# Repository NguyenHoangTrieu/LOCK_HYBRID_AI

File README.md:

# LOCK_HYBRID_AI

Face and RFID attendance / access-control system. A door-mounted **Edge AI Node**
detects faces and reads RFID cards; a **Cloud Backend** identifies people, stores
attendance records, and serves an admin web app. Full detail lives in
[ARCHITECTURE.md](ARCHITECTURE.md) (design) and [SYSTEM_REQUIREMENTS.md](SYSTEM_REQUIREMENTS.md)
(requirements, IEEE 830 / ISO-IEC-IEEE 29148 style). For "what actually
happened and what's still open" across the whole repo (not just one
subproject), see [WORKLOG.md](WORKLOG.md).

## Why the split

The door device can run a small model that finds faces, but not the much
larger model that identifies them, and it can't hold the user database. So
the device answers *"is someone there?"* and the server answers *"who is
it?"* (CON-7, CON-8 in the SRS).

```mermaid
graph LR
    EDGE["Edge AI Node<br/>detects faces, reads cards, opens the latch"]
    CLOUD["Cloud Backend<br/>identifies people, stores records, serves admin UI"]
    EDGE -->|"face image or card UID"| CLOUD
    CLOUD -->|"decision + unlock command"| EDGE
```

## Repository Layout

```
LOCK_HYBRID_AI/
  ARCHITECTURE.md          <- system design, sequence/state diagrams, build order
  SYSTEM_REQUIREMENTS.md   <- SRS: functional, performance, accuracy, safety requirements
  EDGE_NODE/                <- door-side firmware (FRDM-MCXN947 + camera + RFID + LCD + latch)
    Camera_AI_Test1/          <- camera capture + on-device NPU face-detection bring-up project
  PCB_DES/                  <- hardware / PCB design
    LOCK_EDGE_BASEBOARD/
  CLOUD_SERVER/              <- recognition service, database, admin web app (not yet started)
```

### EDGE_NODE

`EDGE_NODE/Camera_AI_Test1` is the bring-up project for the edge device's
camera + on-NPU face-**detection** pipeline (OV7670 → SmartDMA → Edge
Impulse FOMO model on the Neutron NPU → LCD status / SD snapshot), copied
in from the standalone `Camera_AI_Test1` prototype. It proves out CON-1,
CON-3, and CON-7 from the SRS: an FRDM-MCXN947 board driving an OV7670
camera and running face detection on the integrated NPU without the
general-purpose CPU doing the main computation.

This copy keeps its own `README.md` (build/flash instructions, pinout,
hardware notes) and `ARCHITECTURE.md` (design decisions, NPU integration
details), but drops `KNOWLEDGE.md` (a general concepts primer) and
`WORKLOG.md` (the standalone prototype's dated bring-up log) — those
documented the independent history of the prototype and don't apply once
folded into this repo. The firmware source, board port, and AI model files
are unchanged from the original project.

RFID (MFRC522), servo-latch control (fail-locked, HI-3/HI-4/SR-6), the
ARCHITECTURE.md §2.4 state machine, and now the ESP32-C5 network
transport (CON-2, CI-1 to CI-5 - both the ESP-IDF firmware in
`EDGE_NODE/firmware/esp32_net_bridge/` and the MCXN947-side SPI driver)
are implemented and build clean on both sides. None of this has been
flashed to real hardware yet, and the ESP32<->MCXN947 link in particular
has not been verified between two physical boards - see
`EDGE_NODE/firmware/esp32_net_bridge/README.md`. Still missing: offline
event buffering (FR-19 to FR-25) and a real recognition model on the
server (see `CLOUD_SERVER/README.md`).

### CLOUD_SERVER

FastAPI + SQLite implementation of ARCHITECTURE.md §3: device auth, the
face/card attendance API, attendance records with cooldown, and an admin
web app (enrollment, cards, reports, config) - see
[CLOUD_SERVER/README.md](CLOUD_SERVER/README.md). Verified end-to-end
against a running instance, including through the browser UI, not just
written against the spec. The one piece that is a placeholder rather than
real: the recognition model itself (no face-detection/embedding model is
wired in - see that README's Status section before trusting any accuracy
number). Not implemented: TLS termination (put a reverse proxy in front
for real deployment) and offline event buffering on the device side to
actually feed `/attendance/batch`.

### PCB_DES

Hardware/PCB design files for the edge baseboard (`LOCK_EDGE_BASEBOARD`).

## Build Order

See ARCHITECTURE.md §6 for the full sequencing rationale. In short: bring
up peripherals in isolation, stand up a stub server API, wire the network
path end to end, get card-based attendance fully working with no AI
involved, then bring in the detection model on the device and recognition
on the server.

## Known Limitations (by design, this release)

- **No presentation-attack (spoofing) detection** — a photo of an enrolled
  person may be sufficient to obtain access (SR-7). Sites needing
  protection against this must not rely on face recognition as the sole
  access control.
- Face-based access is not available while offline; only card-based access
  can optionally work offline, using cached authorization data (FR-23,
  FR-24).

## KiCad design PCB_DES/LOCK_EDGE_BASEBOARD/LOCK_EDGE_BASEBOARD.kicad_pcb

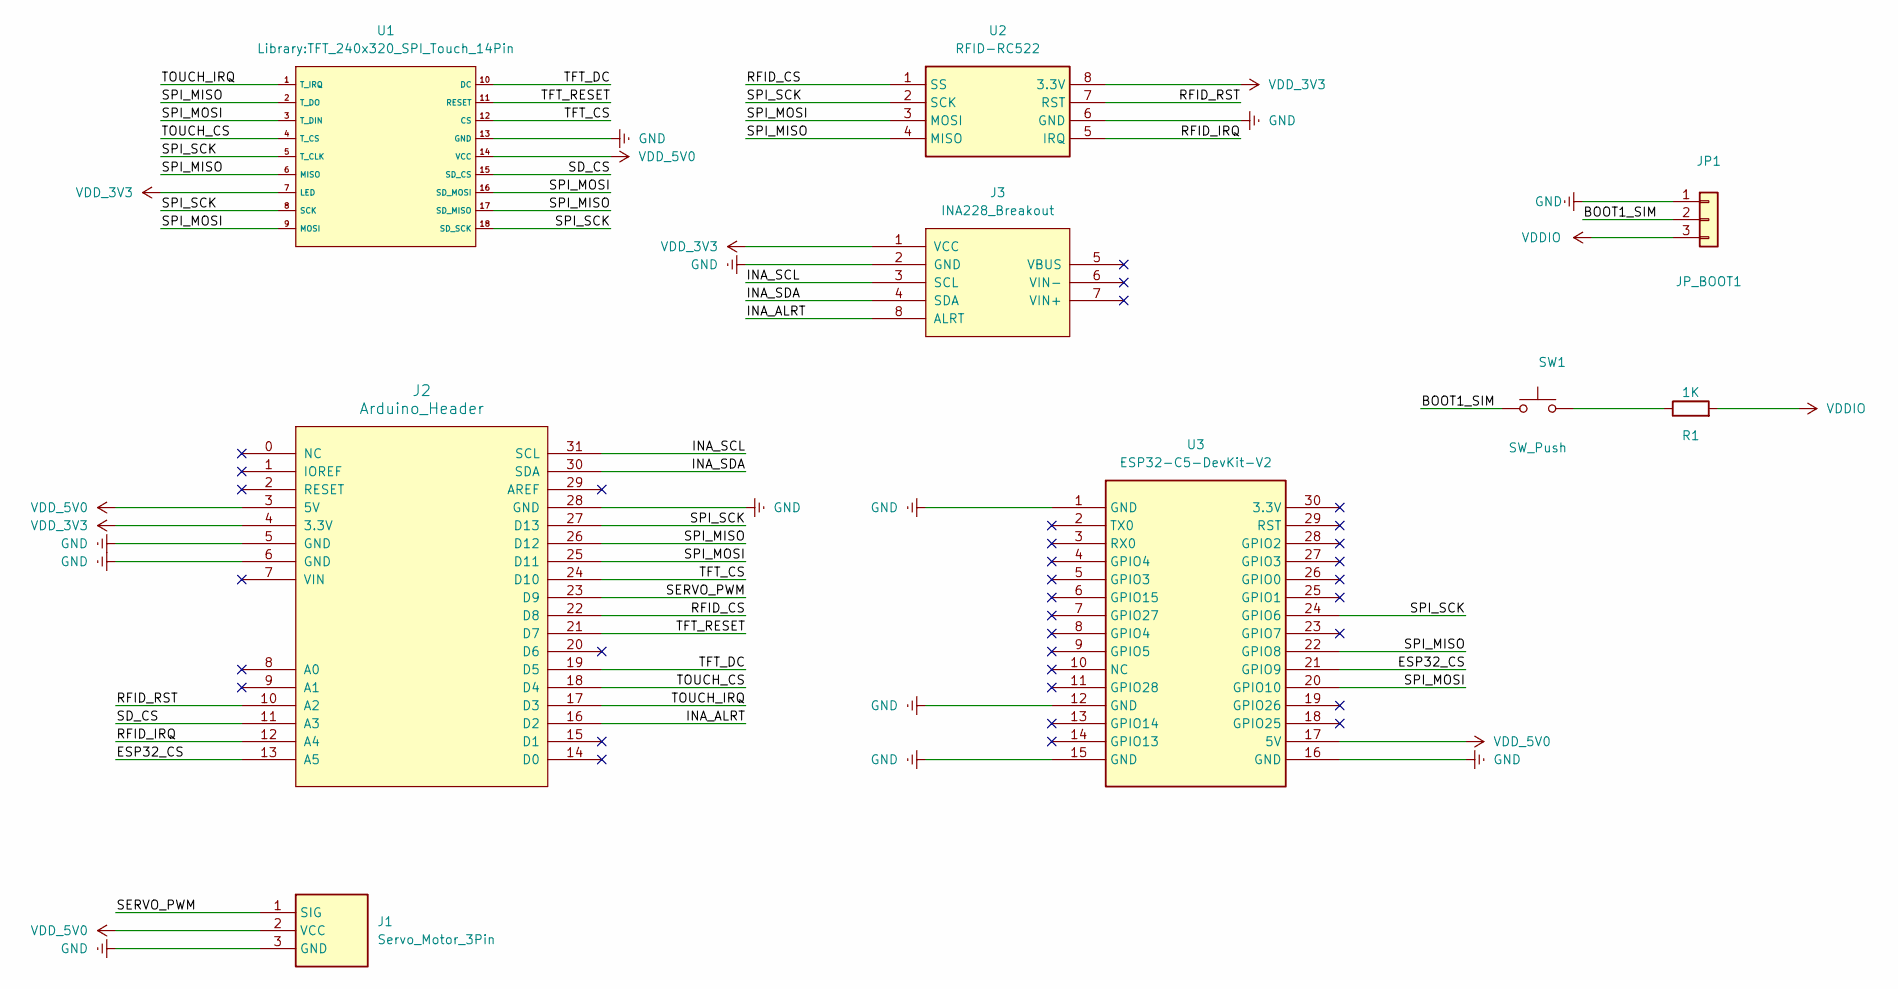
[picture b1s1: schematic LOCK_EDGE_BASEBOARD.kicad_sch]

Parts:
J1: Servo_Motor_3Pin; Servo_Header_1x03_P2.54mm
J2: Arduino_Header
J3: INA228_Breakout; INA228_Breakout_Socket
JP1: JP_BOOT1; JP_Header_1x03_P2.54mm
R1: 1K; R_1206_3216Metric_Pad1.30x1.75mm_HandSolder
SW1: SW_Push; SW_PUSH_6mm
U1: TFT_240x320_SPI_Touch_14Pin
U2: RFID-RC522; RFID-RC522_Header_1x08_P2.54mm
U3: ESP32-C5-DevKit-V2

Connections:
/BOOT1_SIM: JP1.2, SW1.1
/ESP32_CS: J2.13 (A5), U3.21 (GPIO9)
/INA_ALRT: J2.16 (D2), J3.8 (ALRT)
/INA_SCL: J2.31 (SCL), J3.3 (SCL)
/INA_SDA: J2.30 (SDA), J3.4 (SDA)
/RFID_CS: J2.22 (D8), U2.1 (SS)
/RFID_IRQ: J2.12 (A4), U2.5 (IRQ)
/RFID_RST: J2.10 (A2), U2.7 (RST)
/SD_CS: J2.11 (A3), U1.15 (SD_CS)
/SERVO_PWM: J1.1 (SIG), J2.23 (D9)
/SPI_MISO: J2.26 (D12), U1.2 (T_DO), U1.6 (MISO), U1.17 (SD_MISO), U2.4 (MISO), U3.22 (GPIO8)
/SPI_MOSI: J2.25 (D11), U1.3 (T_DIN), U1.9 (MOSI), U1.16 (SD_MOSI), U2.3 (MOSI), U3.20 (GPIO10)
/SPI_SCK: J2.27 (D13), U1.5 (T_CLK), U1.8 (SCK), U1.18 (SD_SCK), U2.2 (SCK), U3.24 (GPIO6)
/TFT_CS: J2.24 (D10), U1.12 (CS)
/TFT_DC: J2.19 (D5), U1.10 (DC)
/TFT_RESET: J2.21 (D7), U1.11 (RESET)
/TOUCH_CS: J2.18 (D4), U1.4 (T_CS)
/TOUCH_IRQ: J2.17 (D3), U1.1 (T_IRQ)
GND: J1.3 (GND), J2.5 (GND), J2.6 (GND), J2.28 (GND), J3.2 (GND), JP1.1, U1.13 (GND), U2.6 (GND), U3.1 (GND), U3.12 (GND), U3.15 (GND), U3.16 (GND)
unnamed: R1.1, SW1.2
VDDIO: JP1.3, R1.2
VDD_3V3: J2.4 (3.3V), J3.1 (VCC), U1.7 (LED), U2.8 (3.3V)
VDD_5V0: J1.2 (VCC), J2.3 (5V), U1.14 (VCC), U3.17 (5V)

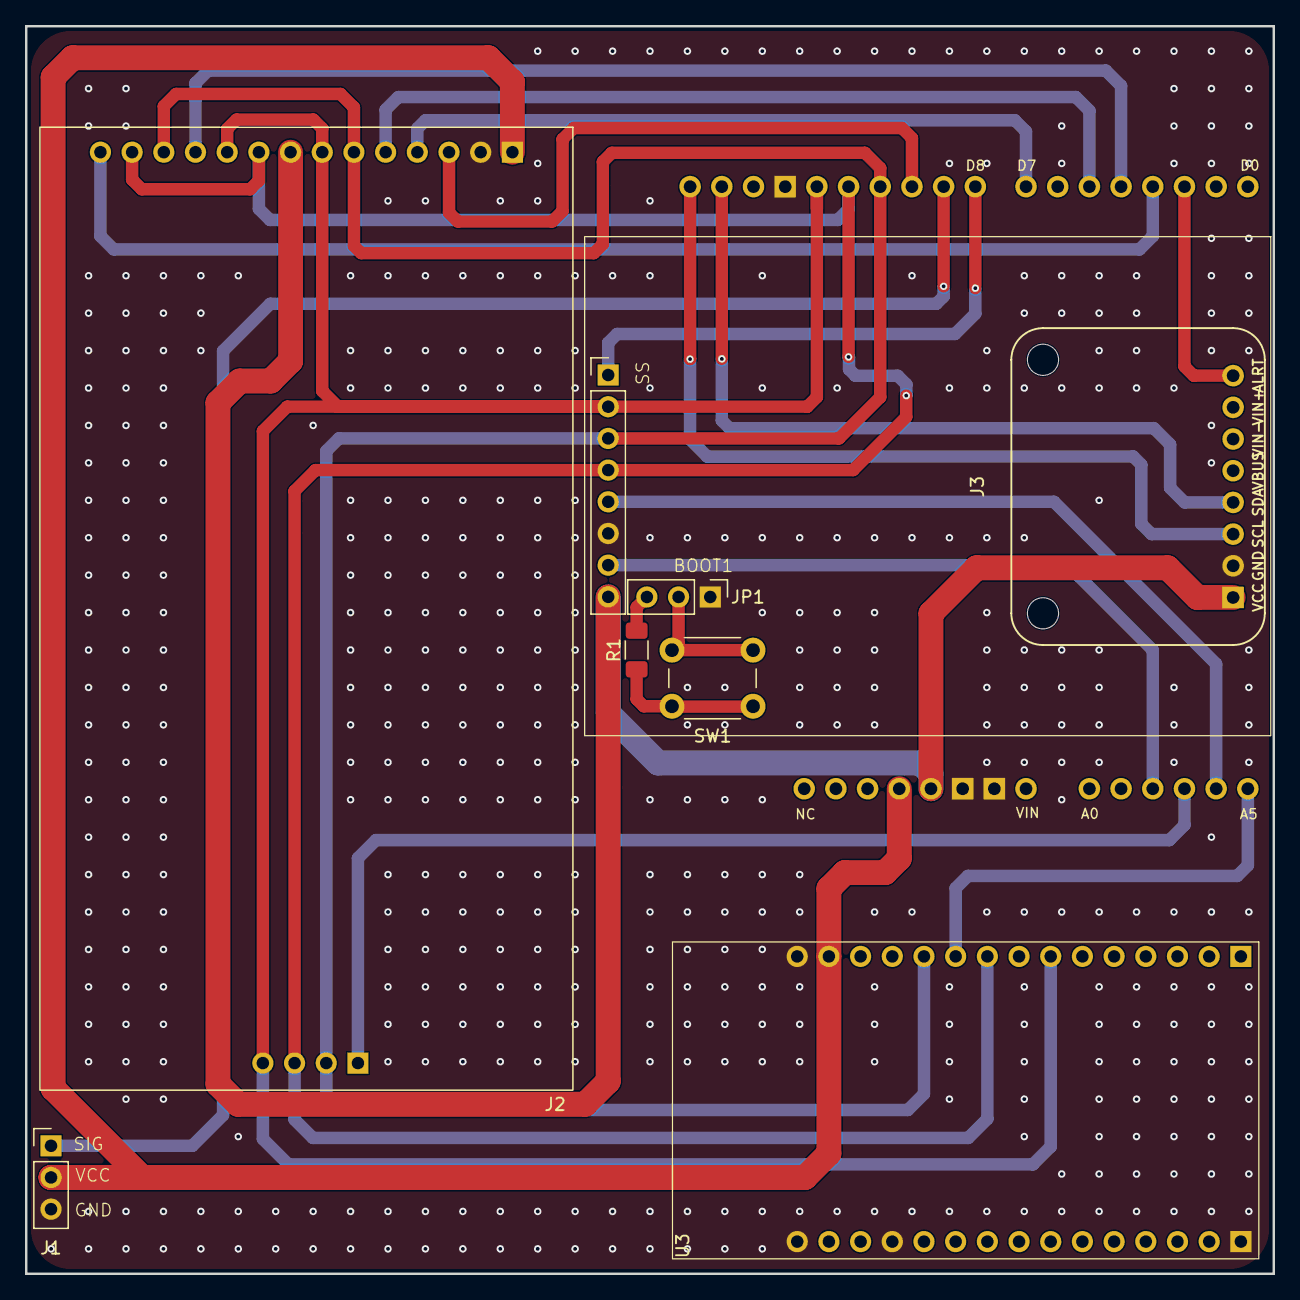
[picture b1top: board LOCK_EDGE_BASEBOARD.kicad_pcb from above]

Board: 2 copper layers, 100.0 x 100.0 mm, 9 parts (0 on the bottom side), 23 nets.

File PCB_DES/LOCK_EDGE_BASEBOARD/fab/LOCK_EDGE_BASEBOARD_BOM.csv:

"Reference","Value","Footprint","Qty","DNP"
"J1","Servo_Motor_3Pin","Library:Servo_Header_1x03_P2.54mm","1",""
"J2","Arduino_Header","Library:Arduino_Header","1",""
"J3","INA228_Breakout","Library:INA228_Breakout_Socket","1",""
"JP1","JP_BOOT1","Library:JP_Header_1x03_P2.54mm","1",""
"R1","1K","Resistor_SMD:R_1206_3216Metric_Pad1.30x1.75mm_HandSolder","1",""
"SW1","SW_Push","Library:SW_PUSH_6mm","1",""
"U1","","Library:TFT_240x320_SPI_Touch_14Pin","1",""
"U2","RFID-RC522","Library:RFID-RC522_Header_1x08_P2.54mm","1",""
"U3","ESP32-C5-DevKit-V2","Library:ESP32-C5-DevKit-V2","1",""

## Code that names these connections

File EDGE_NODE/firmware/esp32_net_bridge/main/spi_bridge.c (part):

/*
 * spi_bridge.c - see spi_bridge.h / protocol.h.
 *
 * Pin assignment below (GPIO6/8/9/10) is read directly from the
 * schematic's symbol pin names for U3 (esp32-c5-devkit-v2:ESP32-C5-DevKit-V2
 * - SPI_SCK/MOSI/MISO/ESP32_CS nets resolve to pins 24/20/22/21, whose
 * symbol pin names are GPIO6/GPIO10/GPIO8/GPIO9), not guessed. The
 * Library README (PCB_DES/LOCK_EDGE_BASEBOARD/Library/README.md) does
 * flag this symbol's physical column spacing/outline as an unmeasured
 * guess, though - if the populated module's actual header doesn't land
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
